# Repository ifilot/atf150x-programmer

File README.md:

# ATF150x programmer

Program **ATF1502AS** and **ATF1504AS** chips with an Arduino Leonardo and a
small open-source adapter board, instead of the expensive ATDH1150USB
programmer and its vendor software.

These chips (CPLDs) hold a small digital-logic design that you create in a tool
such as WinCUPL. That tool produces a `.jed` file; this project writes that
file into the chip and checks that it arrived correctly.

## Contents

- [What you need](#what-you-need)
- [Download](#download)
- [Quick start (Windows)](#quick-start-windows)
- [The desktop application](#the-desktop-application)
- [Command line (Windows and Linux)](#command-line-windows-and-linux)
- [Troubleshooting](#troubleshooting)
- [Technical details](#technical-details)
- [License](#license)

## What you need

- **The adapter board** from [`pcb/atf150X-programmer`](pcb/atf150X-programmer),
  fitted on an **Arduino Leonardo**.
- **A 5 V ATF1502AS or ATF1504AS** in the PLCC-44 socket, with JTAG enabled.
- **A `.jed` file** for your design, for example made with WinCUPL.
- **A USB cable** and a Windows PC for the desktop application, or Windows or
  Linux for the command line.

Not supported: ATF1502ASV/BE and other low-voltage variants, other chip sizes,
several chips in one chain, and chips whose JTAG port has been switched off.

## Download

| What | Download (v0.3.0) |
| --- | --- |
| **Desktop application for Windows** (recommended) | [Installer](https://github.com/ifilot/atf150x-programmer/releases/download/v0.3.0/atf150x-programmer-v0.3.0-windows-x86_64-setup.exe) · [Portable zip](https://github.com/ifilot/atf150x-programmer/releases/download/v0.3.0/atf150x-programmer-v0.3.0-windows-x86_64.zip) |
| Command-line tool | [Windows](https://github.com/ifilot/atf150x-programmer/releases/download/v0.3.0/atfprog-v0.3.0-windows-x86_64.zip) · [Linux](https://github.com/ifilot/atf150x-programmer/releases/download/v0.3.0/atfprog-v0.3.0-linux-x86_64.tar.gz) |
| Arduino Leonardo firmware | [Firmware](https://github.com/ifilot/atf150x-programmer/releases/download/v0.3.0/atf1502-leonardo-firmware-v0.3.0.zip) (already included with the desktop application) |

Newer versions and checksums are on the [latest release
page](https://github.com/ifilot/atf150x-programmer/releases/latest).

## Quick start (Windows)

1. **Install** the desktop application with the installer above.
2. **Insert the chip** while the board is unplugged. Check the orientation.
3. **Plug in** the Arduino by USB and start **ATF150x Programmer**. It finds the
   programmer by itself. The first time, it offers to install the firmware on
   the Arduino: click **Yes**.
4. **Open** your `.jed` file with **Open JEDEC…** or by dragging it onto the
   window.
5. Click **Program**. The chip is erased, programmed and checked, which takes
   tens of seconds. Do not unplug the board while it runs.

The status bar and the log at the bottom tell you whether it succeeded.

## The desktop application

<table>
  <tr>
    <td width="50%"></td>
    <td width="50%"></td>
  </tr>
  <tr>
    <td>An ATF1502AS design, fitted to the window.</td>
    <td>Zoomed in; the cell under the mouse is described below the map.</td>
  </tr>
</table>

- **Program, Verify, Erase, Identify.** *Verify* compares the chip with the
  open file without changing it. *Identify* reports which chip is in the
  socket. If you rebuild the `.jed` file in WinCUPL, it is reloaded
  automatically before programming.
- **Fuse map.** Shows every memory cell of the chip, colored by what it does.
  Hover over a cell to see its meaning. The side panel summarizes the design:
  chip type, how much of the chip is used, and whether the checksum is valid.
- **Firmware updates.** If the Arduino runs an older or different program, the
  application offers to install the right firmware. The Arduino's bootloader
  is never changed.
- **Update notification.** At startup the application checks for a newer
  release; turn this off in the **Help** menu.

## Command line (Windows and Linux)

`atfprog` does the same as the desktop application from a terminal. Replace
`COM3` with your Arduino's port (on Linux, for example `/dev/ttyACM0`). In
Windows PowerShell, type `.\atfprog.exe` instead of `atfprog`.

```sh
atfprog inspect design.jed            # check the file; does not touch the chip
atfprog scan --port COM3              # identify the chip
atfprog flash design.jed --port COM3  # erase, program and check
atfprog verify design.jed --port COM3 # compare chip and file
atfprog erase --port COM3             # erase the chip
atfprog --help
```

`flash` checks the `.jed` file before it touches the chip, and switches the new
design on only after every bit has been read back and compared. If programming
is interrupted, reconnect and run `flash` again. A nonzero exit status means
the operation failed.

## Troubleshooting

- **"No Arduino Leonardo found" or the port is busy.** Close the Arduino IDE
  Serial Monitor and other programs using the port, then press the refresh
  button.
- **The chip reads as all zeros or all ones.** Check that the chip is seated the
  right way round, the board is assembled correctly and the chip is a 5 V
  ATF1502AS/ATF1504AS. A chip with JTAG switched off cannot be recovered with
  this programmer.
- **Linux: permission denied on `/dev/ttyACM0`.** Add your user to the serial
  group (usually `dialout`), then log out and in again.
- **Programming was interrupted.** Nothing is switched on until the design has
  been checked; simply program again.

## Technical details

- [Building from source](docs/BUILDING.md): firmware, command-line tool and
  desktop application.
- [Protocol and programming algorithm](docs/PROTOCOL.md): supported JEDEC
  records, fuse mapping, serial framing and safeguards.
- [Validation](docs/VALIDATION.md) on real hardware, including
  cross-checks with an official ATDH1150USB programmer, and matching
  [WinCUPL test designs](examples/logic_test/README.md).
- [Coding style](docs/STYLE.md) and
  [third-party attribution](docs/THIRD_PARTY.md).

<details>
<summary>Board pin assignments</summary>

| JTAG | Leonardo pin | Series resistor |
| --- | --- | --- |
| TDI | D2 | R3 |
| TCK | D3 | R4 |
| TDO | D4 | R5 |
| TMS | D12 | R6 |

The board uses ordinary GPIO pins, not the Leonardo's SPI header. Its `5V1` pin
supplies the `+5V` net. The firmware leaves the JTAG pins as inputs between
sessions and does not switch the chip's power. ATF1502AS reports IDCODE
`0x0150203F`; ATF1504AS reports `0x0150403F`.

</details>

## License

The software, firmware, tests, build configuration and documentation are
licensed under the GNU General Public License version 3 only
(`GPL-3.0-only`); see [LICENSE](LICENSE). Copyright (c) 2026 ATF1502 programmer
contributors. Required upstream notices are kept in
[third-party attribution](docs/THIRD_PARTY.md). The PCB files keep their
[CC BY-SA 4.0 license](pcb/atf150X-programmer/LICENSE).

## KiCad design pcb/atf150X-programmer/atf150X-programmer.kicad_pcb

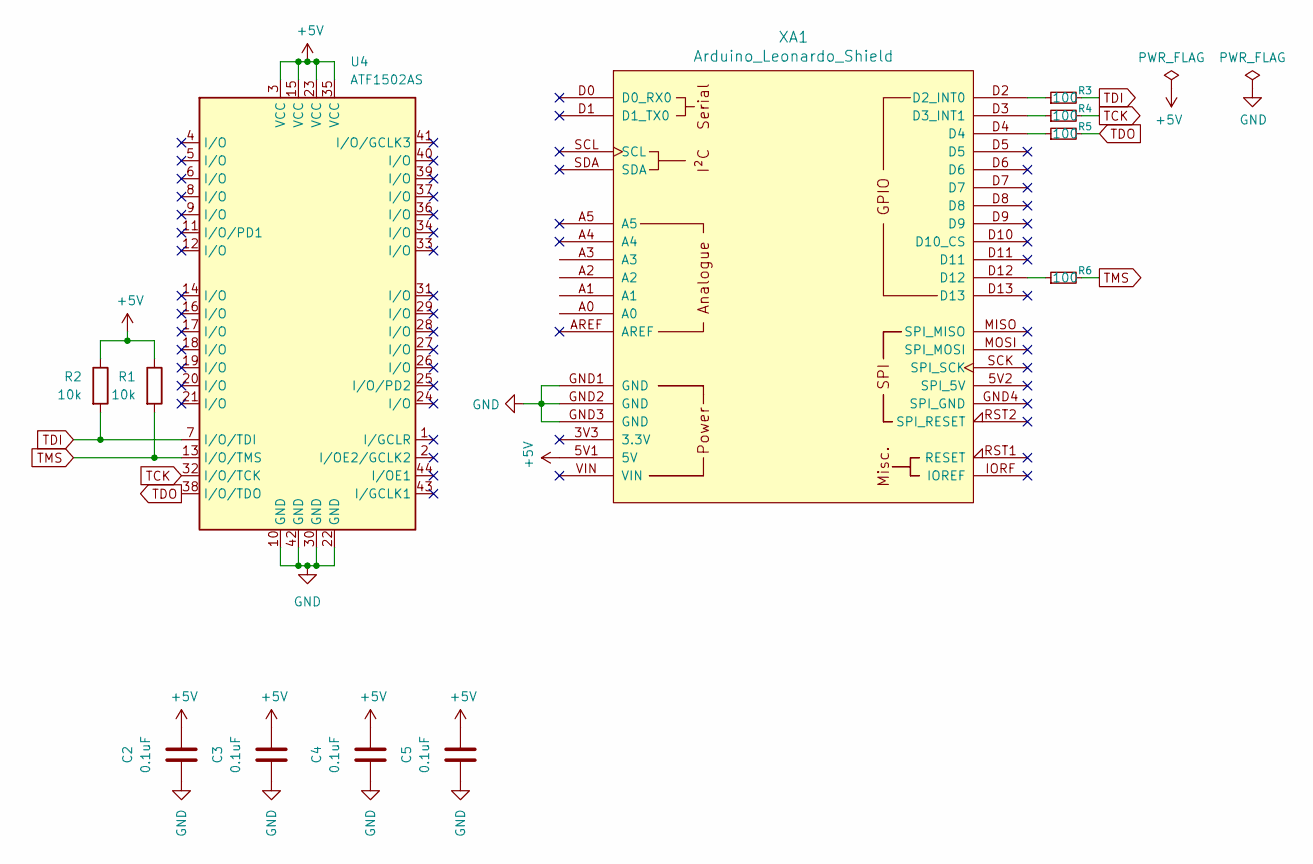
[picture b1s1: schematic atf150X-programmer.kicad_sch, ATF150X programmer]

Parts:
C2, C3, C4, C5: 0.1uF; C_Disc_D5.0mm_W2.5mm_P5.00mm
R1, R2: 10k; R_Axial_DIN0207_L6.3mm_D2.5mm_P7.62mm_Horizontal
R3, R4, R5, R6: 100; R_Axial_DIN0207_L6.3mm_D2.5mm_P7.62mm_Horizontal
U4: ATF1502AS; PLCC-44_THT-Socket
XA1: Arduino_Leonardo_Shield; Arduino_Uno_Shield

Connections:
+5V: C2.1, C3.1, C4.1, C5.1, R1.1, R2.1, U4.3 (VCC), U4.15 (VCC), U4.23 (VCC), U4.35 (VCC), XA1.5V1 (5V)
GND: C2.2, C3.2, C4.2, C5.2, U4.10 (GND), U4.22 (GND), U4.30 (GND), U4.42 (GND), XA1.GND1 (GND), XA1.GND2 (GND), XA1.GND3 (GND)
unnamed: R5.1, XA1.D4
unnamed: R6.1, XA1.D12
unnamed: R3.1, XA1.D2 (D2_INT0)
unnamed: R4.1, XA1.D3 (D3_INT1)
TCK: R4.2, U4.32 (I/O/TCK)
TDI: R2.2, R3.2, U4.7 (I/O/TDI)
TDO: R5.2, U4.38 (I/O/TDO)
TMS: R1.2, R6.2, U4.13 (I/O/TMS)

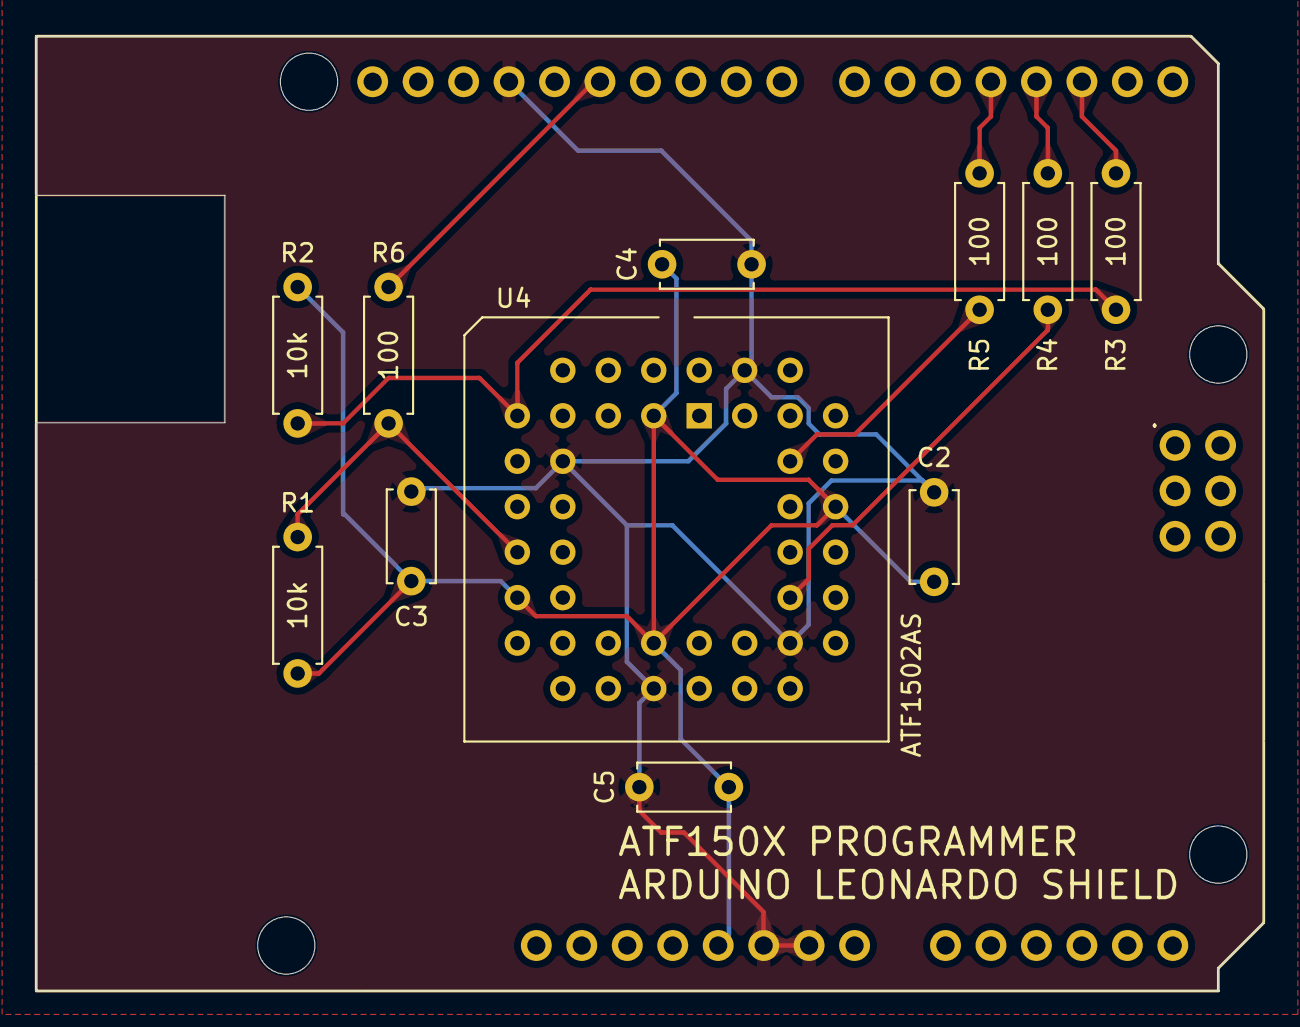
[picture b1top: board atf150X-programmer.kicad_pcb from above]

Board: 2 copper layers, 68.6 x 53.3 mm, 12 parts (0 on the bottom side), 10 nets.

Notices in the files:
README.md:
License: GPL v3
